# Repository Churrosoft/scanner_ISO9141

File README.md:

# scanner_ISO9141
OBDII interface for ISO 9141, serial and usb

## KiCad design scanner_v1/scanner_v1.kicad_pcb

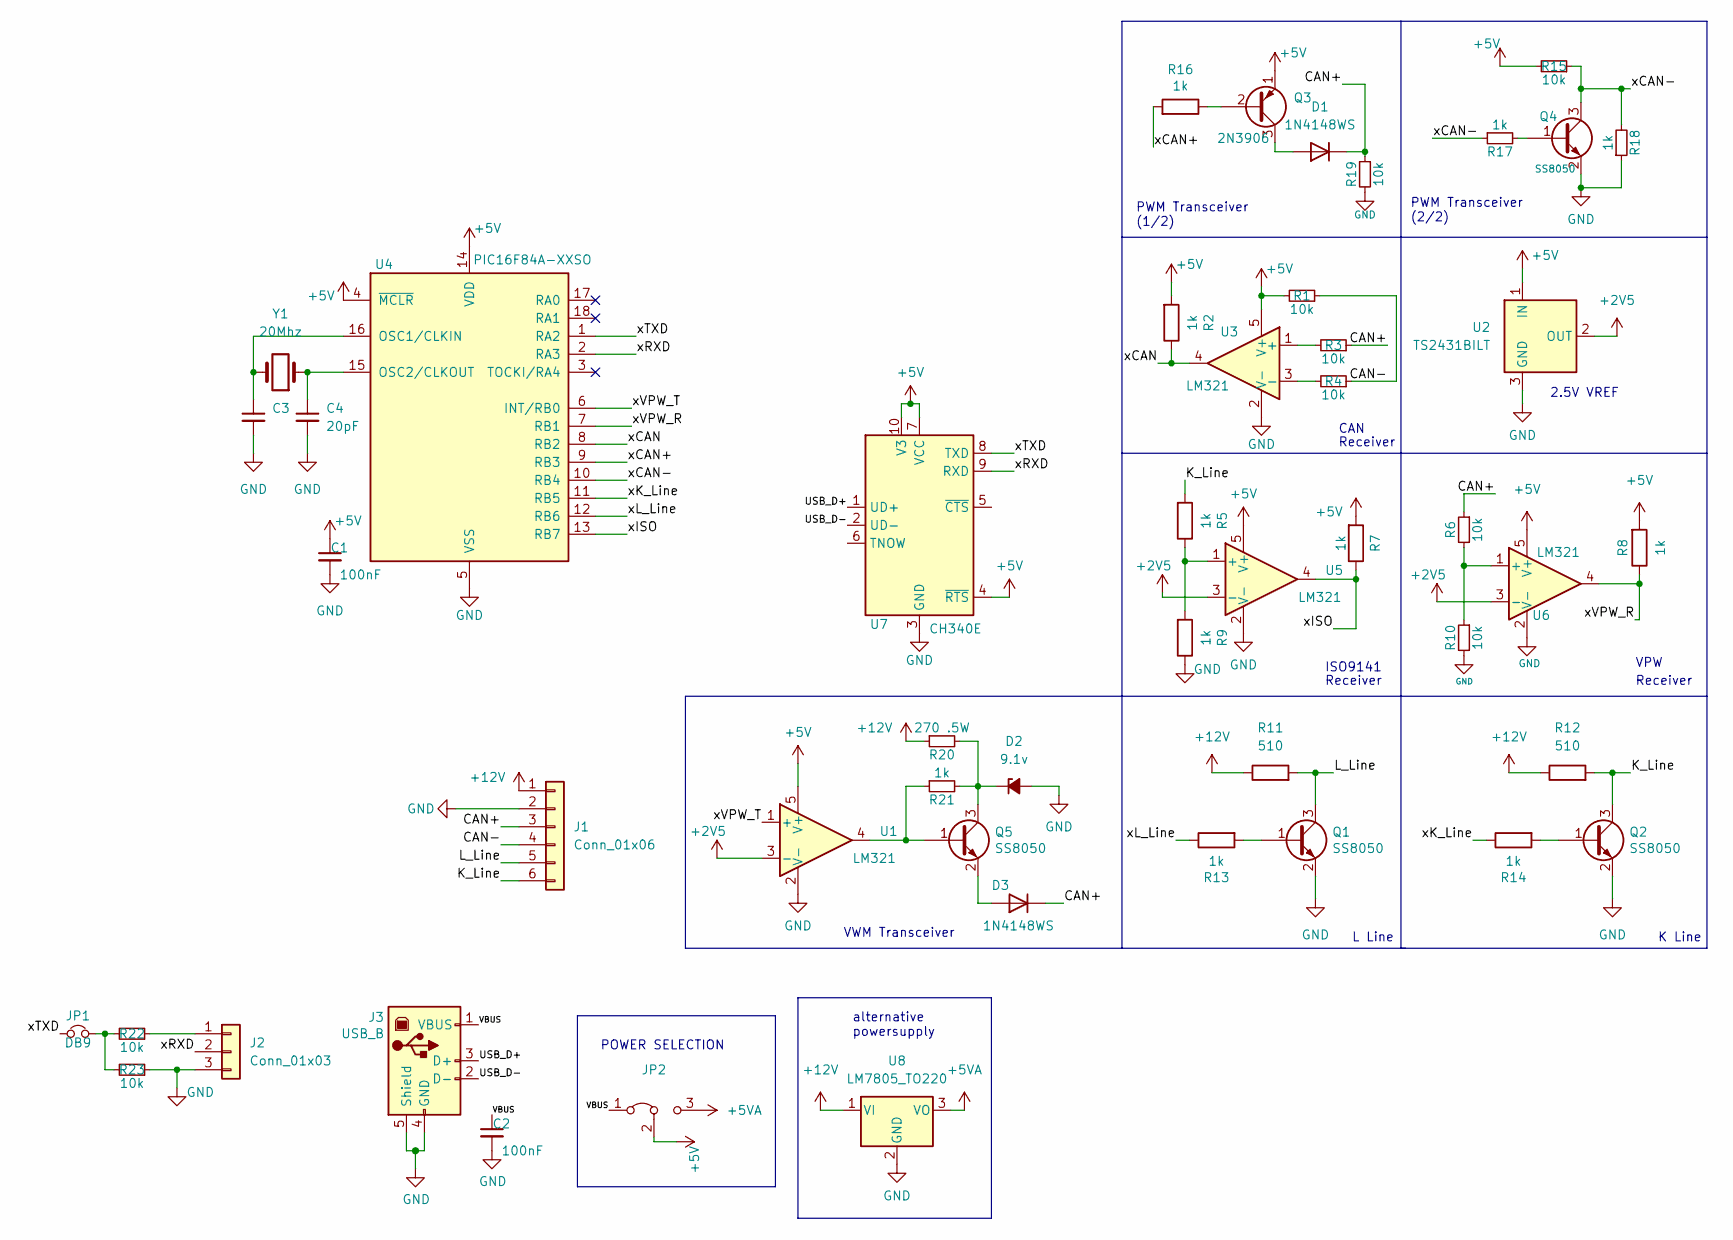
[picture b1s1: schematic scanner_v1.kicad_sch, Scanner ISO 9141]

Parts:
C1, C2: 100nF; C_0805_2012Metric; LCSC C49678
C3, C4: 20pF; C_0603_1608Metric; LCSC C56475
D1, D3: 1N4148WS; D_SOD-323; LCSC C110221
D2: 9.1v; D_SOD-123; LCSC C438333
J1: Conn_01x06; PinHeader_1x06_P2.54mm_Vertical
J2: Conn_01x03; PinHeader_1x03_P2.54mm_Vertical
J3: USB_B; USB_B_OST_USB-B1HSxx_Horizontal
JP1: DB9; SolderJumper-2_P1.3mm_Open_TrianglePad1.0x1.5mm
JP2: Jumper_3_Bridged12; SolderJumper-3_P1.3mm_Bridged2Bar12_RoundedPad1.0x1.5mm_Num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
Q1, Q2, Q4, Q5: SS8050; SOT-23; LCSC C2150
Q3: 2N3906; SOT-23
R1, R3, R4, R6, R10, R15, R19, R22, R23: 10k; R_0603_1608Metric; LCSC C25804
R2, R5, R7, R8, R9, R13, R14, R16, R17, R18, R21: 1k; R_0603_1608Metric; LCSC C21190
R11, R12: 510; R_0603_1608Metric; LCSC C173329
R20: 270 .5W; R_1206_3216Metric; LCSC C966064
U1, U3, U5, U6: LM321; SOT-23-5
U2: TS2431BILT; SOT-23; LCSC C283636
U4: PIC16F84A-XXSO; SSOP-18_4.4x6.5mm_P0.65mm; LCSC C184204
U7: CH340E; MSOP-10_3x3mm_P0.5mm
U8: LM7805_TO220; TO-220-3_Vertical
Y1: 20Mhz; Crystal_HC49-4H_Vertical; LCSC C252298

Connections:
+2V5: U1.3 (-), U2.2 (OUT), U5.3 (-), U6.3 (-)
+5V: C1.1, JP2.2 (C), Q3.1 (E), R1.2, R2.2, R7.2, R8.2, R15.2, U1.5 (V+), U2.1 (IN), U3.5 (V+), U4.4 (~MCLR), U4.14 (VDD), U5.5 (V+), U6.5 (V+), U7.4 (~RTS), U7.7 (VCC), U7.10 (V3)
+5VA: JP2.3 (B), U8.3 (VO)
+12V: J1.1, R11.1, R12.1, R20.1, U8.1 (VI)
/CAN+: D1.1 (K), D3.1 (K), J1.3, R3.1, R6.1, R19.1
/CAN-: J1.4, R1.1, R4.1
/K_Line: J1.6, Q2.3 (C), R5.2, R12.2
/L_Line: J1.5, Q1.3 (C), R11.2
/USB_D+: J3.3 (D+), U7.1 (UD+)
/USB_D-: J3.2 (D-), U7.2 (UD-)
/VBUS: C2.1, J3.1 (VBUS), JP2.1 (A)
/xCAN: R2.1, U3.4, U4.8 (RB2)
/xCAN+: R16.2, U4.9 (RB3)
/xCAN-: Q4.3 (C), R15.1, R17.1, R18.2, U4.10 (RB4)
/xISO: R7.1, U4.13 (RB7), U5.4
/xK_Line: R14.1, U4.11 (RB5)
/xL_Line: R13.1, U4.12 (RB6)
/xRXD: J2.2, U4.2 (RA3), U7.9 (RXD)
/xTXD: JP1.1, U4.1 (RA2), U7.8 (TXD)
/xVPW_R: R8.1, U4.7 (RB1), U6.4
/xVPW_T: U1.1 (+), U4.6 (INT/RB0)
GND: C1.2, C2.2, C3.2, C4.2, D2.2 (A), J1.2, J2.3, J3.4 (GND), J3.5 (Shield), Q1.2 (E), Q2.2 (E), Q4.2 (E), R9.1, R10.2, R18.1, R19.2, R23.1, U1.2 (V-), U2.3 (GND), U3.2 (V-), U4.5 (VSS), U5.2 (V-), U6.2 (V-), U7.3 (GND), U8.2 (GND)
unnamed: C3.1, U4.16 (OSC1/CLKIN), Y1.2
unnamed: C4.1, U4.15 (OSC2/CLKOUT), Y1.1
unnamed: D1.2 (A), Q3.3 (C)
unnamed: D2.1 (K), Q5.3 (C), R20.2, R21.2
unnamed: D3.2 (A), Q5.2 (E)
unnamed: J2.1, R22.1
unnamed: JP1.2, R22.2, R23.2
unnamed: Q1.1 (B), R13.2
unnamed: Q2.1 (B), R14.2
unnamed: Q3.2 (B), R16.1
unnamed: Q4.1 (B), R17.2
unnamed: Q5.1 (B), R21.1, U1.4
unnamed: R3.2, U3.1 (+)
unnamed: R4.2, U3.3 (-)
unnamed: R5.1, R9.2, U5.1 (+)
unnamed: R6.2, R10.1, U6.1 (+)

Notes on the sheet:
POWER SELECTION
VWM Transceiver
alternative powersupply
PWM Transceiver (1/2)
ISO9141
Receiver
CAN
L Line
PWM Transceiver (2/2)
2.5V VREF
VPW
K Line

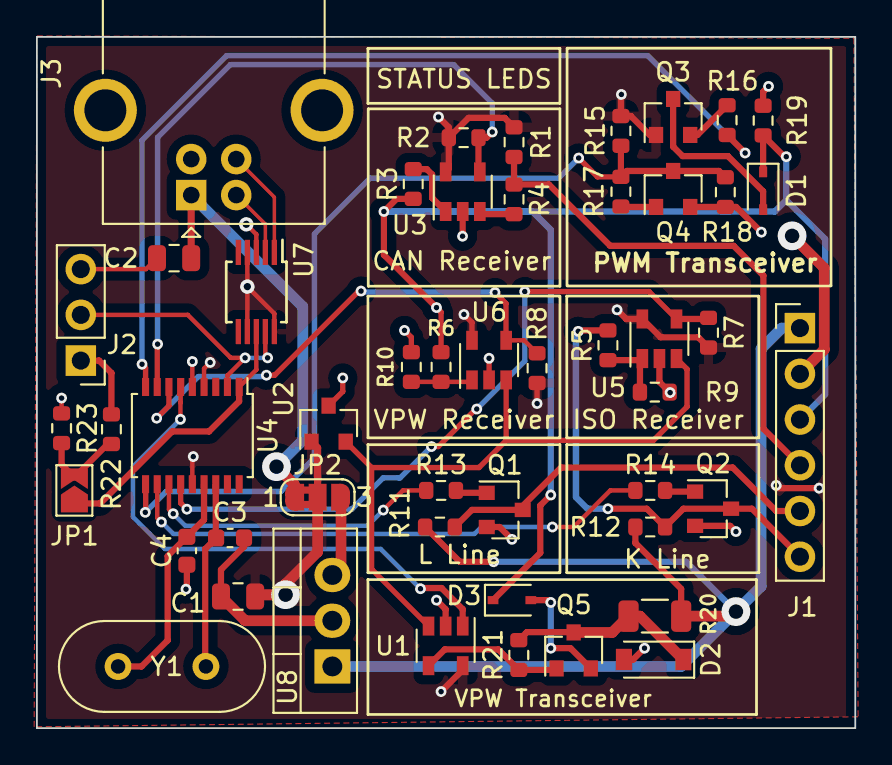
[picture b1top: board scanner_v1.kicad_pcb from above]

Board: 2 copper layers, 45.5 x 38.4 mm, 50 parts (1 on the bottom side), 38 nets.

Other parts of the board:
Churrosoft: LOGO; churrosoft

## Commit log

2021-09-18 init eschematic, added usb=>serial and changes on VREF
2021-09-18 added ISO/VPW/PWM receivers
2021-09-21 finish v01
2021-09-21 v1, fix on RST pin
